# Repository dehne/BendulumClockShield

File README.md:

# Bendulum Clock Shield

Bendulum Clock Shield Copyright 2014 by D. L. Ehnebuske  
License terms: [Creative Commons Attribution-ShareAlike 3.0 United States (CC BY-SA 3.0 US)]
(http://creativecommons.org/licenses/by-sa/3.0/us/ "CC BY-SA 3.0 US")

This is the more complex of two Arduino shields that implement the hardware interface between an 
Arduino Uno that drives a bendulum clock and the rest of the bendulum clock. The other is the 
EscapementShield. This one is more complex in that it implements a battery backup. If the power 
fails, the clock keeps going!

The Rev H version adds a header for the Sparkfun TMP-102 temperature sensor (for temperature 
compensated operation) and removes the potentiometers for the clock and coil as experiments 
have shown it is possible to get the needed control in software.

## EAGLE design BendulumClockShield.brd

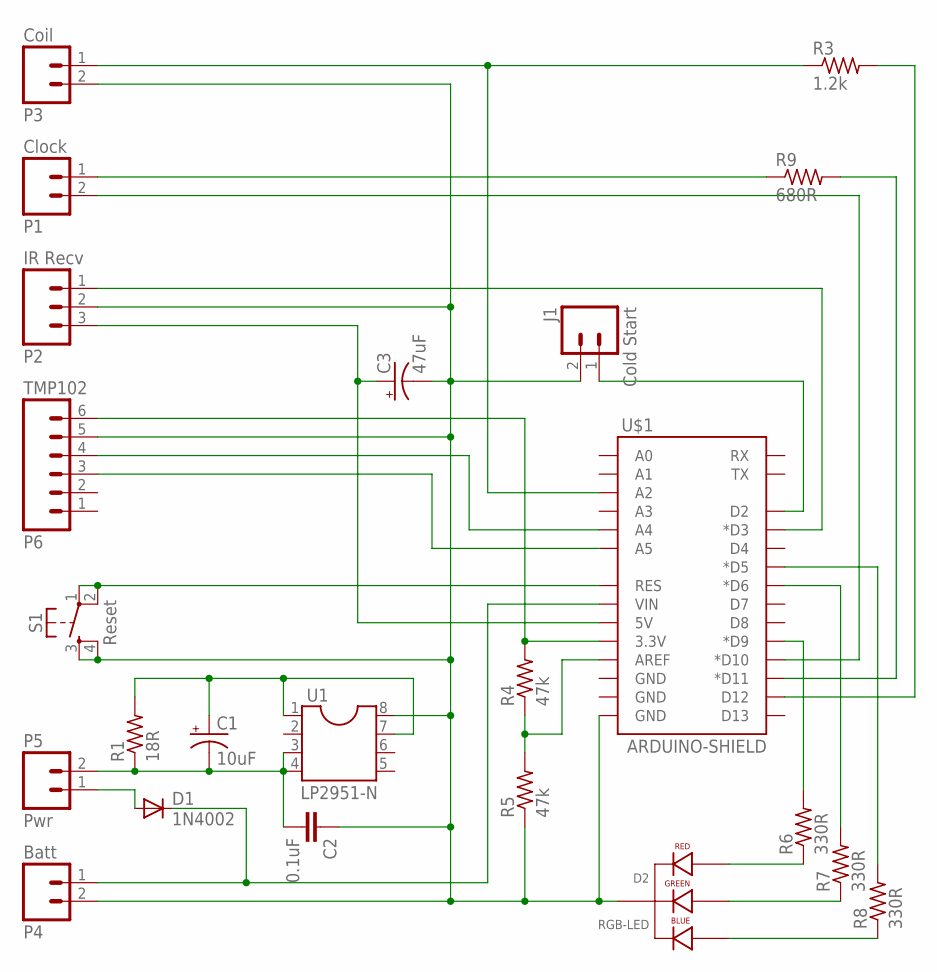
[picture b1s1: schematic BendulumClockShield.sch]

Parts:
C1: 10uF; CPOL-RADIAL-10UF-25V
C2: 0.1uF; CAP-PTH-5MM
C3: 47uF; CPOL-RADIAL-10UF-25V
D1: 1N4002; DIODE-1N4001-KIT
D2: RGB-LED; LED-RGB-THRU
J1: Cold Start; 1X02
P1: Clock; 1X02
P2: IR Recv; 1X03
P3: Coil; 1X02
P4: Batt; 1X02
P5: Pwr; 1X02
R1: 18R; AXIAL-0.4
R3: 1.2k; AXIAL-0.4
R4, R5: 47k; AXIAL-0.4
R6, R7, R8: 330R; AXIAL-0.4
R9: 680R; AXIAL-0.4
S1: Reset; TACTILE-PTH
TMP102: P6; 1X06
U1: LP2951-N; SOCKET-08
U$1: ARDUINO-SHIELD; DUEMILANOVE_SHIELD

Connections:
GND: C2.1, C3.2 (-), D2.2 (CATHODE), J1.2, P2.2, P3.2, P4.2, R5.P$1 (1), S1.3, S1.4, TMP102.5, U1.8 (INPUT), U$1.GND@0 (GND)
unnamed: D1.A, P5.1
unnamed: D1.C, P4.1, U$1.VIN
unnamed: C1.2 (-), C2.2, P5.2, R1.P$1 (1), U1.3 (SHUTDOWN), U1.4 (GND)
unnamed: S1.1, S1.2, U$1.RES
unnamed: R6.P$2 (2), U$1.D9 (*D9)
unnamed: P3.1, R3.P$1 (1), U$1.A2
unnamed: R4.P$2 (2), TMP102.6, U$1.3.3V
unnamed: R3.P$2 (2), U$1.D12
unnamed: TMP102.4, U$1.A4
unnamed: J1.1, U$1.D2
unnamed: R4.P$1 (1), R5.P$2 (2), U$1.AREF
unnamed: R7.P$2 (2), U$1.D6 (*D6)
unnamed: R8.P$2 (2), U$1.D5 (*D5)
unnamed: P2.1, U$1.D3 (*D3)
unnamed: C3.1 (+), P2.3, U$1.5V
unnamed: TMP102.3, U$1.A5
unnamed: D2.1 (RED_ANODE), R6.P$1 (1)
unnamed: D2.3 (GREEN_ANODE), R7.P$1 (1)
unnamed: D2.4 (BLUE_ANODE), R8.P$1 (1)
unnamed: P1.2, U$1.D10 (*D10)
unnamed: P1.1, R9.P$1 (1)
unnamed: R9.P$2 (2), U$1.D11 (*D11)
U1: C1.1 (+), R1.P$2 (2), U1.1 (OUTPUT), U1.7 (FEEDBACK)

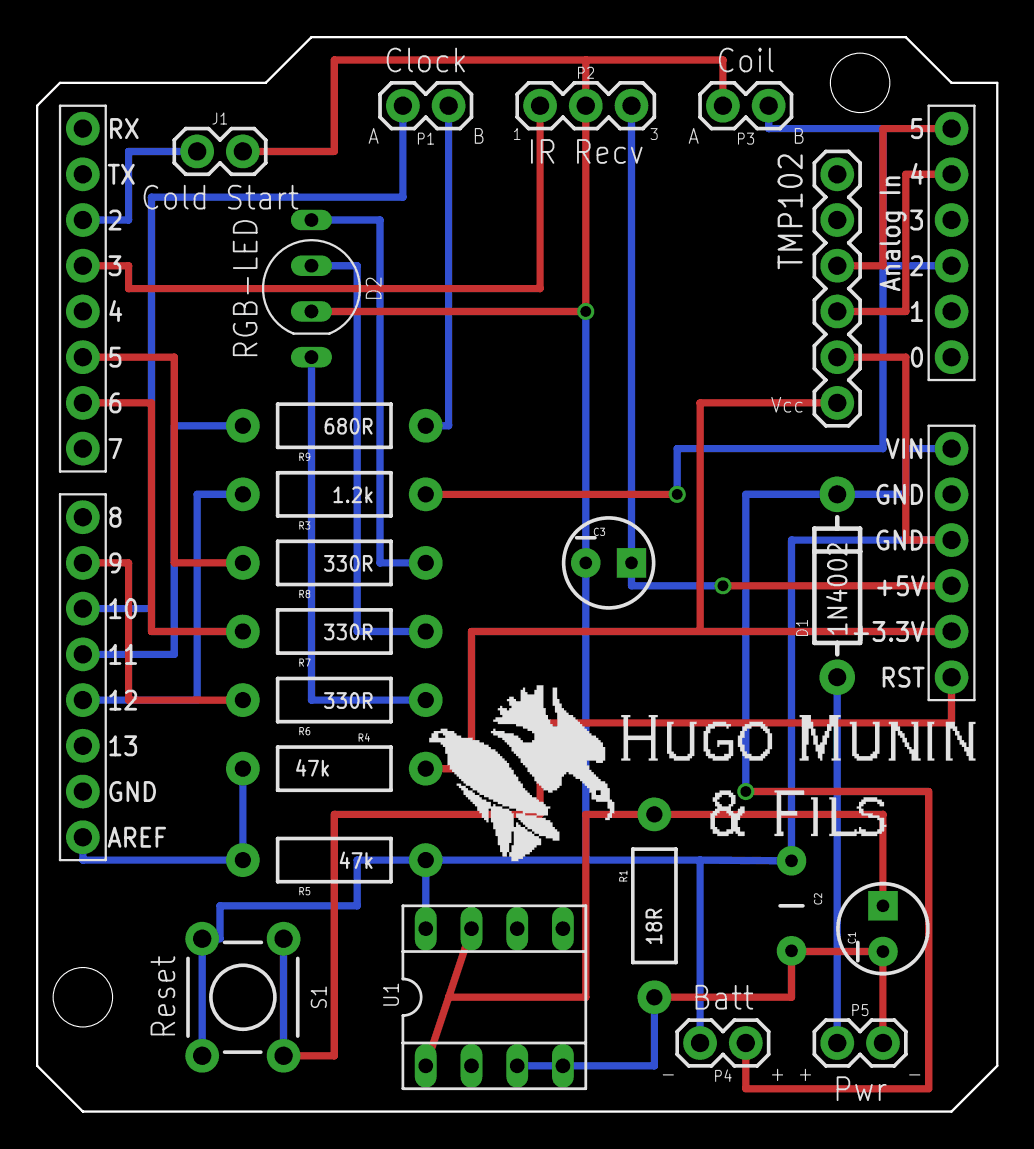
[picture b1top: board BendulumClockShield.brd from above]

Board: 2 copper layers, 53.3 x 59.7 mm, 24 parts (0 on the bottom side), 24 nets.

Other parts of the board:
U$2: HMF-LOGO

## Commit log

2014-04-25 origin
    Initial commit
2014-04-26 Add schematic
    Add the conventional schematic for the clock shield
2014-04-30 Update to Rev G
    Increase current drive to 68mA; 42mA for the Arduino and 26mA to keep
    the the battery pack fully charged. (26mA is 0.01C for 2500mAh
    batteries.)
2014-10-10 Update to Rev H
    Add header for TMP-102 temperature sensor
2014-10-10 Add Rev H schematic
    Add schematic as a pdf
2014-10-10 CHG: Documentation for Rev H
    Explain what changed in Rev H

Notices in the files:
parts and their libraries:
SparkFun-DiscreteSemi: Licensing: CC v3.0 Share-Alike You are welcome to use this library for commercial purposes.
